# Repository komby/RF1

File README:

For more information visit: http://www.komby.com/RF1

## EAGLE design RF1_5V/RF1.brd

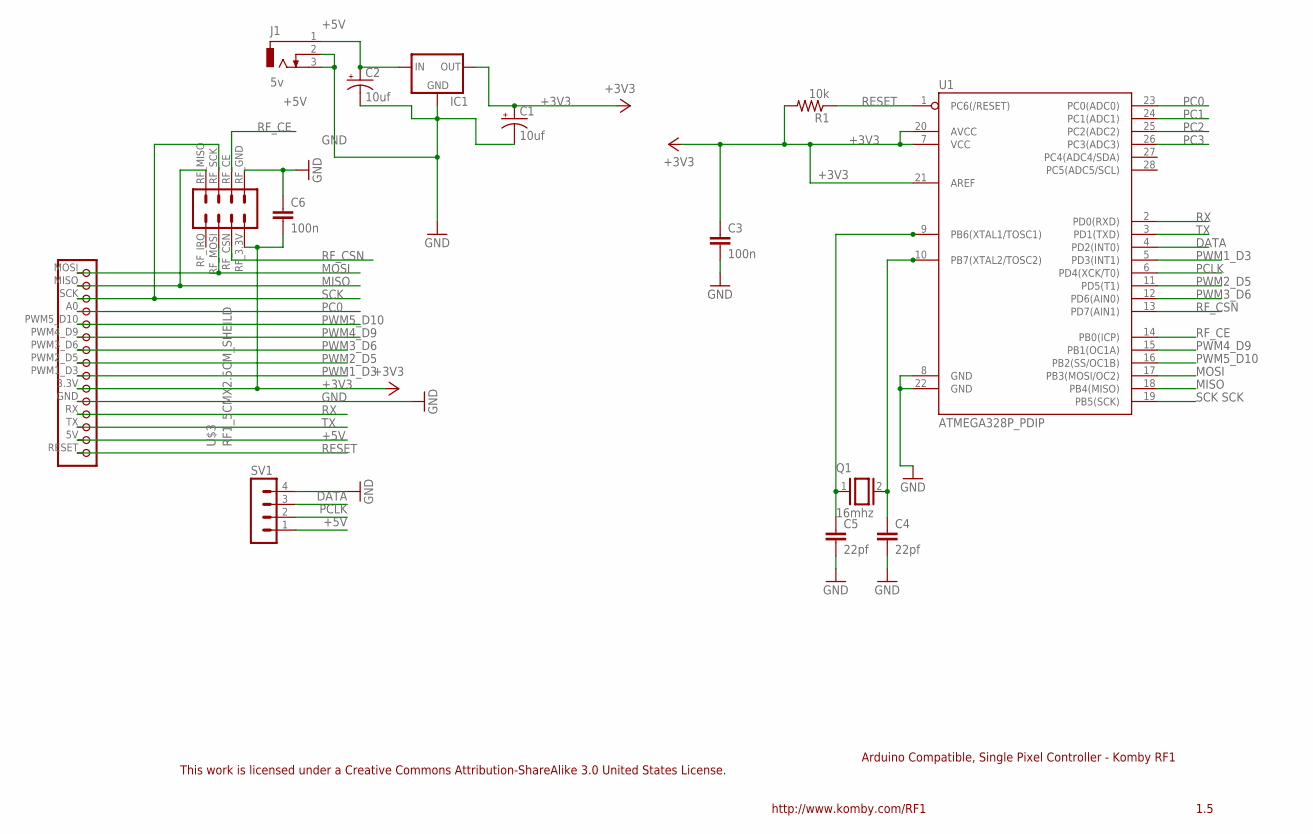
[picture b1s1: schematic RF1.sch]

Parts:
C1, C2: 10uf; E1,8-4
C3, C6: 100n; C025-024X044
C4, C5: 22pf; C025-024X044
IC1: MCP1700TRI; TO92
J1: 5v; DCJ0303
Q1: 16mhz; QS
R1: 10k; 0207/7
SV1: MA04-1
U1: ATMEGA328P_PDIP; DIL28-3
U$3: RF1_5CMX2.5CM_SHEILD; KOMBY_RF1_SHEILD_5X2.5

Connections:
+3V3: C1.+, C3.1, C6.2, IC1.3 (OUT), R1.2, U1.7 (VCC), U1.20 (AVCC), U1.21 (AREF), U$3.3.3V, U$3.RF_3.3V
+5V: C2.+, IC1.2 (IN), J1.1, SV1.1, U$3.5V
DATA: SV1.3, U1.4 (PD2(INT0))
GND: C1.-, C2.-, C3.2, C4.2, C5.2, C6.1, IC1.1 (GND), J1.2, J1.3, SV1.4, U1.8 (GND), U1.22 (GND), U$3.GND, U$3.RF_GND (RFGND_1)
MISO: U1.18 (PB4(MISO)), U$3.MISO, U$3.RF_MISO
MOSI: U1.17 (PB3(MOSI/OC2)), U$3.MOSI, U$3.RF_MOSI
unnamed: C4.1, Q1.2, U1.10 (PB7(XTAL2/TOSC2))
unnamed: C5.1, Q1.1, U1.9 (PB6(XTAL1/TOSC1))
PC0: U1.23 (PC0(ADC0)), U$3.A0 (PC0)
PC1: U1.24 (PC1(ADC1))
PC2: U1.25 (PC2(ADC2))
PC3: U1.26 (PC3(ADC3))
PCLK: SV1.2, U1.6 (PD4(XCK/T0))
PWM1_D3: U1.5 (PD3(INT1)), U$3.PWM1_D3 (PWM1)
PWM2_D5: U1.11 (PD5(T1)), U$3.PWM2_D5 (PWM2)
PWM3_D6: U1.12 (PD6(AIN0)), U$3.PWM3_D6 (PWM3)
PWM4_D9: U1.15 (PB1(OC1A)), U$3.PWM4_D9 (PWM4)
PWM5_D10: U1.16 (PB2(SS/OC1B)), U$3.PWM5_D10 (PWM5)
RESET: R1.1, U1.1 (PC6(/RESET)), U$3.RESET
RF_CE: U1.14 (PB0(ICP)), U$3.RF_CE
RF_CSN: U1.13 (PD7(AIN1)), U$3.RF_CSN
RX: U1.2 (PD0(RXD)), U$3.RX
SCK: U1.19 (PB5(SCK)), U$3.RF_SCK, U$3.SCK
TX: U1.3 (PD1(TXD)), U$3.TX

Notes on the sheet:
Arduino Compatible, Single Pixel Controller - Komby RF1
1.5
http://www.komby.com/RF1
This work is licensed under a Creative Commons Attribution-ShareAlike 3.0 United States License.

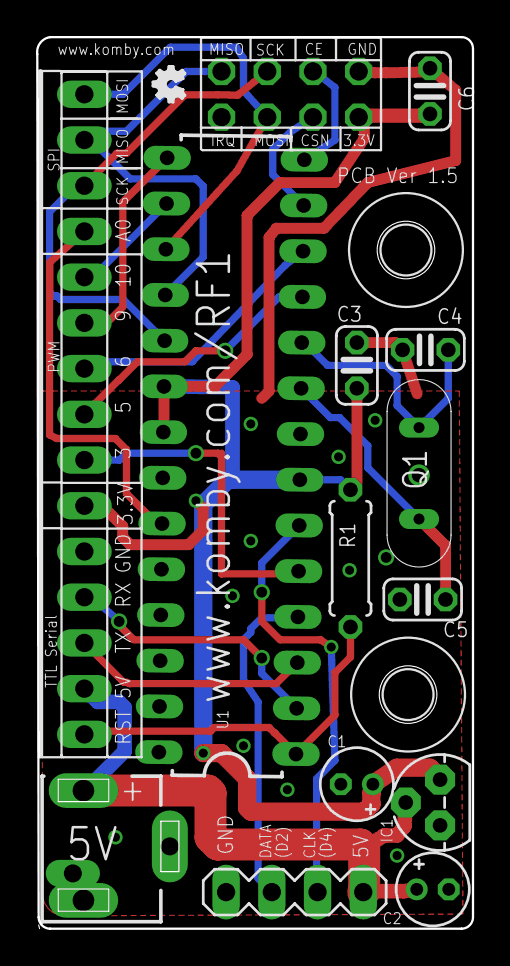
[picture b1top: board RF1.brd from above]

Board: 2 copper layers, 24.2 x 49.5 mm, 14 parts (0 on the bottom side), 21 nets.

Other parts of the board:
U$1: OSHW_FILLX70_NOTEXT

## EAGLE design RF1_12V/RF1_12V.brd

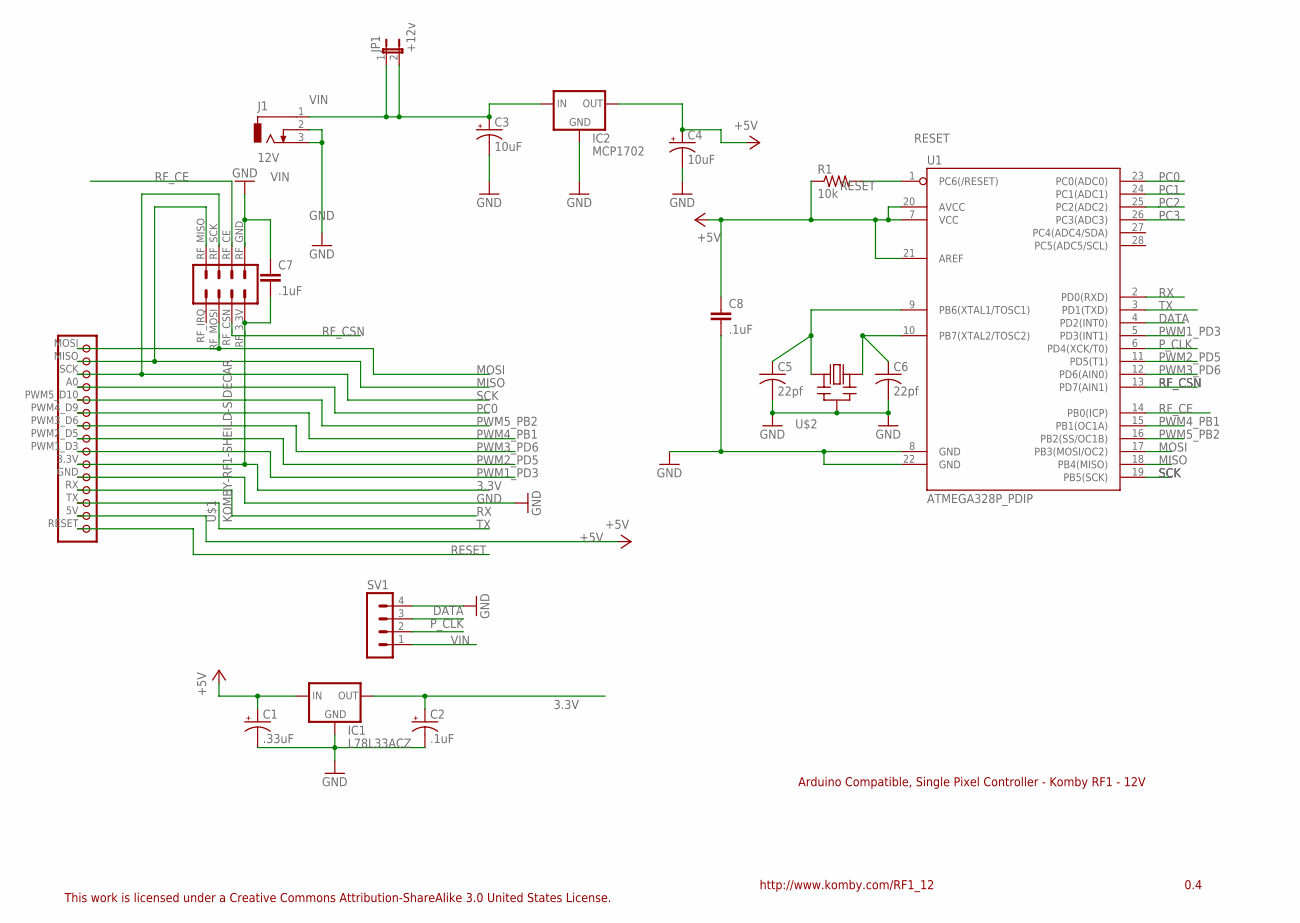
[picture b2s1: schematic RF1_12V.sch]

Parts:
C1: .33uF; E1,8-4
C2: .1uF; E1,8-4
C3, C4: 10uF; E1,8-4
C5, C6: 22pf; C0805
C7, C8: .1uF; C025-024X044
IC1: L78L33ACZ; 78LXX
IC2: MCP1702; TO92
J1: 12V; DCJ0303
JP1: +12v; JP1
R1: 10k; 0207/7
SV1: MA04-1
U1: ATMEGA328P_PDIP; DIL28-3
U$1: KOMBY-RF1-SHEILD-SIDECAR; KOMBY-RF1-SIDECAR
U$2: CERMOSCILL-THM; CERM_OSC

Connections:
3.3V: C2.+, C7.2, IC1.OUT, U$1.3.3V, U$1.RF_3.3V
+5V: C1.+, C4.+, C8.1, IC1.IN, IC2.3 (OUT), R1.1, U1.7 (VCC), U1.20 (AVCC), U1.21 (AREF), U$1.5V
DATA: SV1.3, U1.4 (PD2(INT0))
GND: C1.-, C2.-, C3.-, C4.-, C5.2, C6.2, C7.1, C8.2, IC1.GND, IC2.1 (GND), J1.2, J1.3, SV1.4, U1.8 (GND), U1.22 (GND), U$1.GND, U$1.RF_GND (RFGND_1), U$2.P$2 (GND)
MISO: U1.18 (PB4(MISO)), U$1.MISO, U$1.RF_MISO
MOSI: U1.17 (PB3(MOSI/OC2)), U$1.MOSI, U$1.RF_MOSI
unnamed: C6.1, U1.10 (PB7(XTAL2/TOSC2)), U$2.P$3 (OUT)
unnamed: C5.1, U1.9 (PB6(XTAL1/TOSC1)), U$2.P$1 (IN)
PC0: U1.23 (PC0(ADC0)), U$1.A0 (PC0)
PC1: U1.24 (PC1(ADC1))
PC2: U1.25 (PC2(ADC2))
PC3: U1.26 (PC3(ADC3))
PWM1_PD3: U1.5 (PD3(INT1)), U$1.PWM1_D3 (PWM1)
PWM2_PD5: U1.11 (PD5(T1)), U$1.PWM2_D5 (PWM2)
PWM3_PD6: U1.12 (PD6(AIN0)), U$1.PWM3_D6 (PWM3)
PWM4_PB1: U1.15 (PB1(OC1A)), U$1.PWM4_D9 (PWM4)
PWM5_PB2: U1.16 (PB2(SS/OC1B)), U$1.PWM5_D10 (PWM5)
P_CLK: SV1.2, U1.6 (PD4(XCK/T0))
RESET: R1.2, U1.1 (PC6(/RESET)), U$1.RESET
RF_CE: U1.14 (PB0(ICP)), U$1.RF_CE
RF_CSN: U1.13 (PD7(AIN1)), U$1.RF_CSN
RX: U1.2 (PD0(RXD)), U$1.RX
SCK: U1.19 (PB5(SCK)), U$1.RF_SCK, U$1.SCK
TX: U1.3 (PD1(TXD)), U$1.TX
VIN: C3.+, IC2.2 (IN), J1.1, JP1.1, JP1.2, SV1.1

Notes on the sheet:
Arduino Compatible, Single Pixel Controller - Komby RF1 - 12V
0.4
http://www.komby.com/RF1_12
This work is licensed under a Creative Commons Attribution-ShareAlike 3.0 United States License.

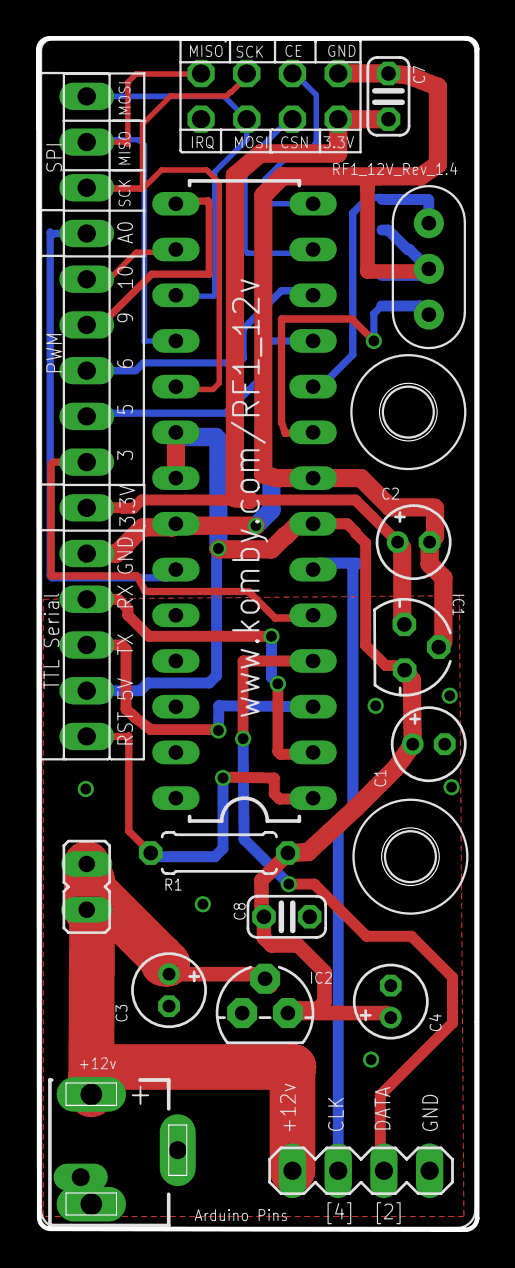
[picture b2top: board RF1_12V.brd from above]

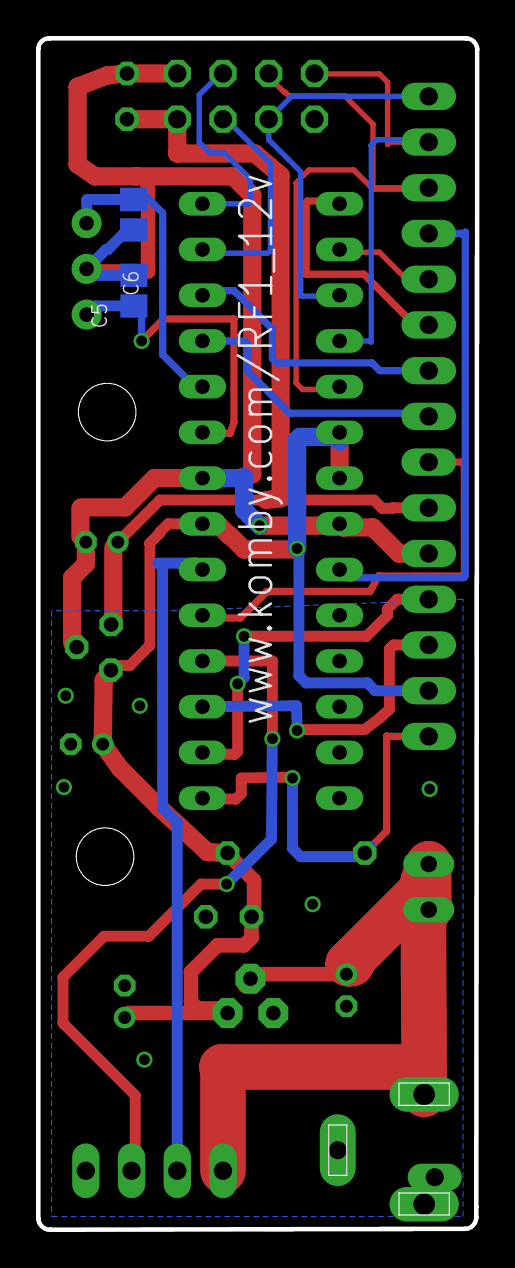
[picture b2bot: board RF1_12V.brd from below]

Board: 2 copper layers, 24.4 x 66.2 mm, 17 parts (2 on the bottom side), 22 nets.

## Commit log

2013-05-06 Initial Release
2013-06-17 Updated Revised layout of RF1 board
2013-06-17 Added RF1_5V and RF1_12V folders and relocated boards and Schematics
2013-06-17 updated revision information
2014-02-08 Updated with 2014 designs for both RF1_12v and RF1 5v

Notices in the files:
parts and their libraries:
SparkFun-DigitalIC: Licensing: CC v3.0 Share-Alike You are welcome to use this library for commercial purposes.
